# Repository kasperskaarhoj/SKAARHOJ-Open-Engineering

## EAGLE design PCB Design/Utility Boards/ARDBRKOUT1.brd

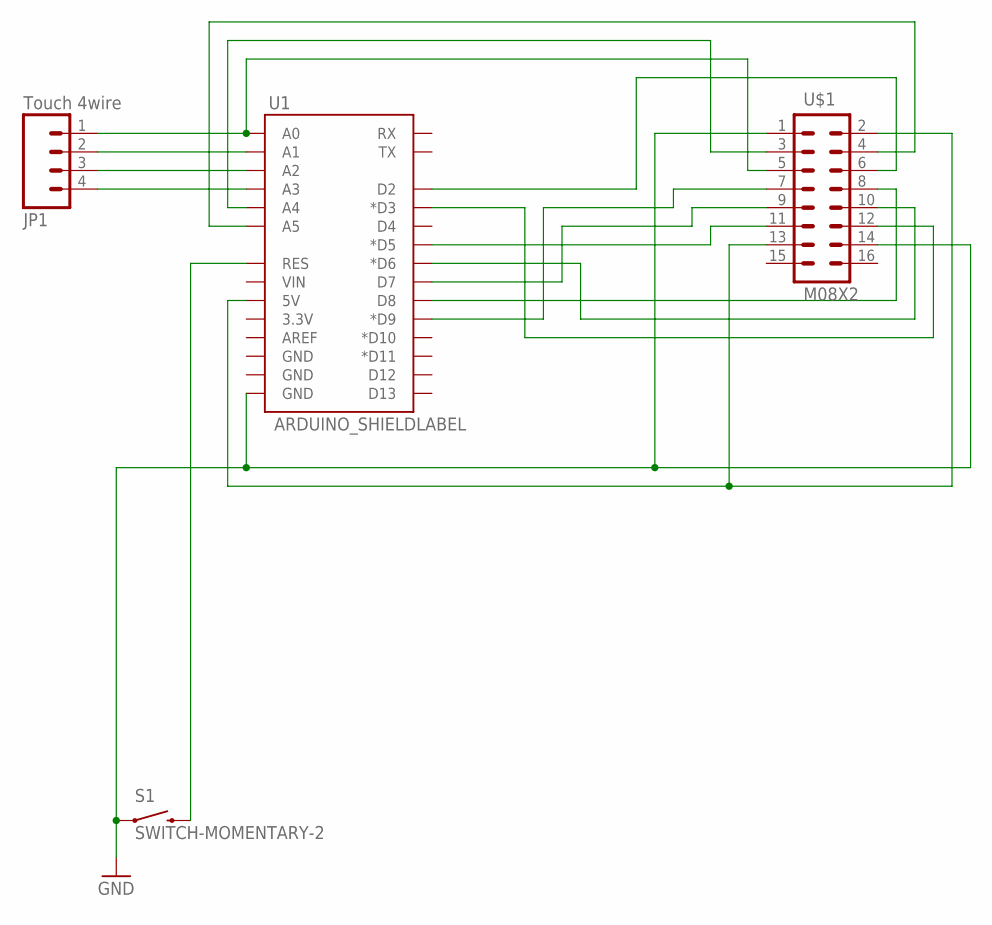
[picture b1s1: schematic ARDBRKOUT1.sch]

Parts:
JP1: Touch 4wire; 1X04
S1: SWITCH-MOMENTARY-2; TACTILE_SWITCH_TALL
U1: ARDUINO_SHIELDLABEL; DUEMILANOVE_SHIELD
U$1: M08X2; 2X8

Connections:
GND: S1.A2 (1), U1.GND@0 (GND), U$1.1, U$1.14
unnamed: U1.D9 (*D9), U$1.7
unnamed: U1.5V, U$1.2, U$1.13
unnamed: U1.A4, U$1.3
unnamed: U1.A5, U$1.4
unnamed: JP1.1, U1.A0, U$1.5
unnamed: U1.D2, U$1.6
unnamed: U1.D5 (*D5), U$1.11
unnamed: U1.D8, U$1.8
unnamed: U1.D7, U$1.9
unnamed: U1.D6 (*D6), U$1.10
unnamed: JP1.2, U1.A1
unnamed: U1.D3 (*D3), U$1.12
unnamed: JP1.3, U1.A2
unnamed: JP1.4, U1.A3
unnamed: S1.B2 (2), U1.RES

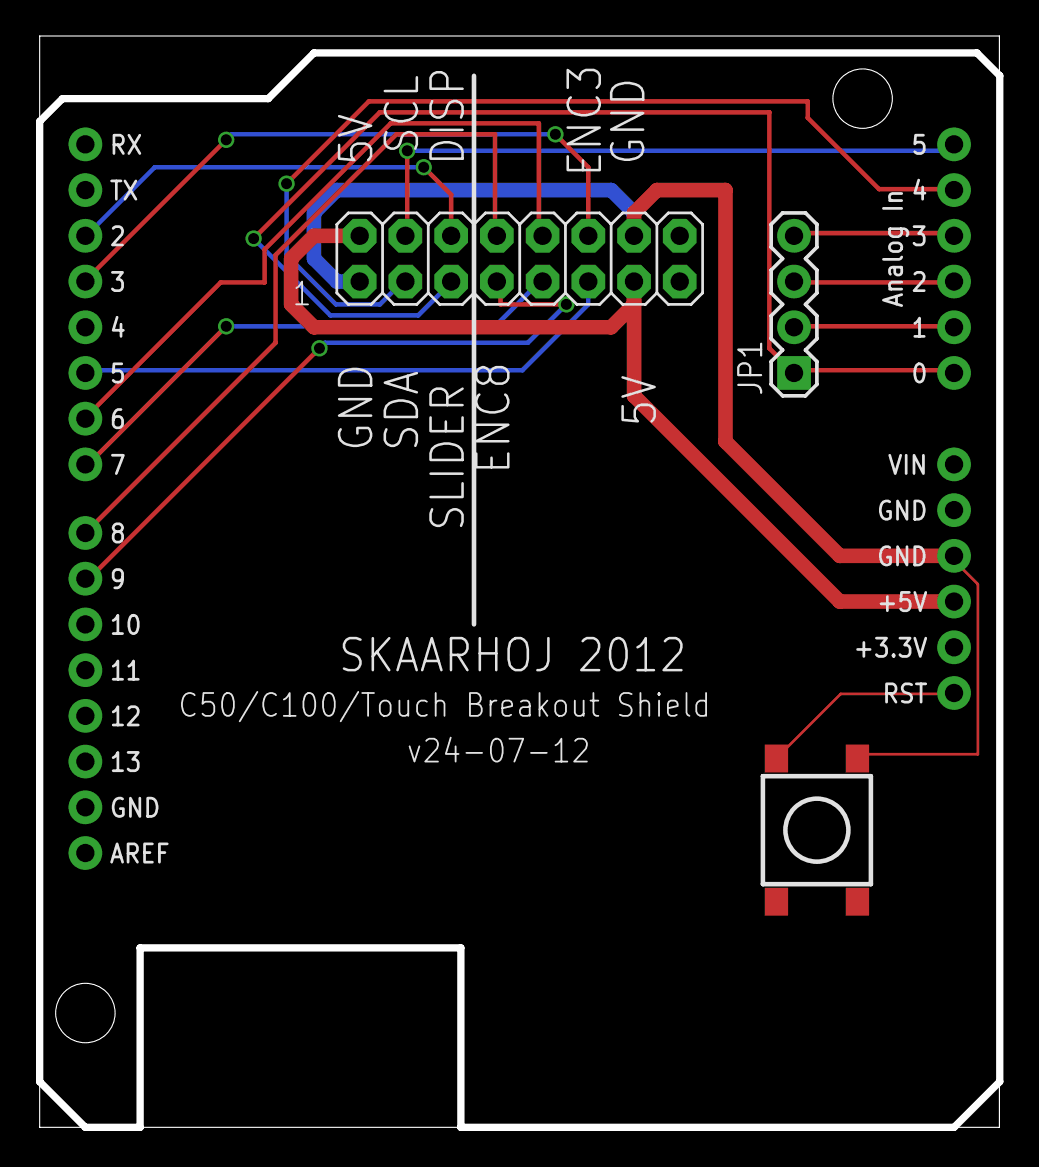
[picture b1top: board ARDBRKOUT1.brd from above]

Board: 2 copper layers, 53.3 x 60.6 mm, 4 parts (0 on the bottom side), 16 nets.

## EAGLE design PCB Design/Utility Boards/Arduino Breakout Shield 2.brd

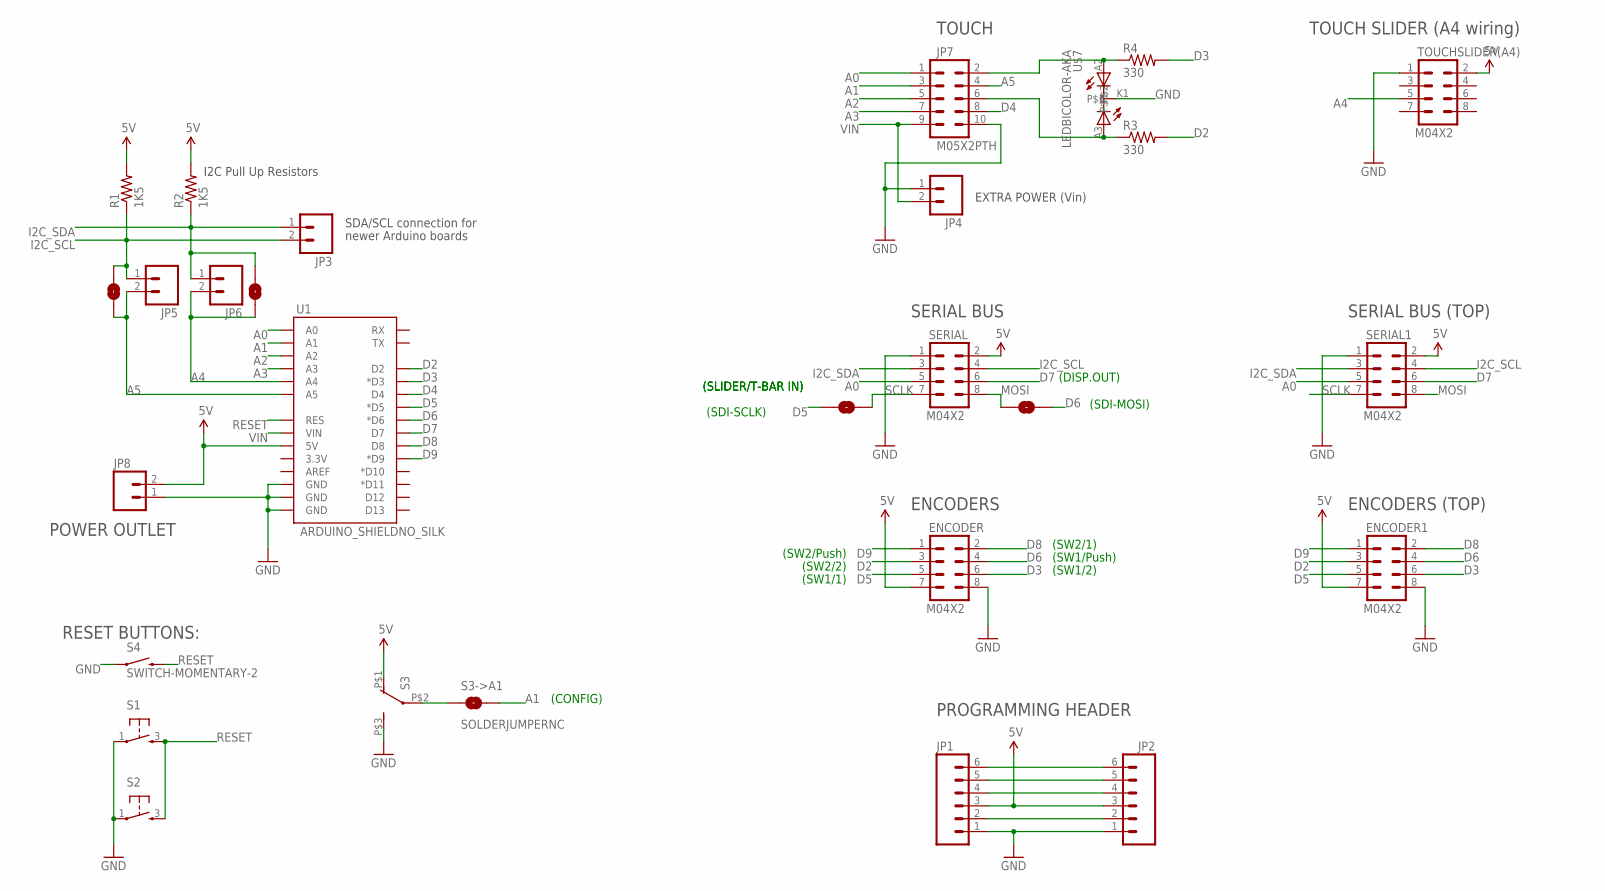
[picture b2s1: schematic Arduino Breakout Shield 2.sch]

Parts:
ENCODER, ENCODER1: M04X2; 2X4
JP1, JP2: M06POLAR; MOLEX-1X6
JP3, JP4, JP5, JP6: M02PTH; 1X02
JP7: M05X2PTH; AVR_ICSP
JP8: M02PTH4; 1X02_XTRA_BIG
MOSI->D6: SOLDERJUMPERNC; SJ_2S
R1, R2: 1K5; 0603-RES
R3, R4: 330; AXIAL-0.4
S1, S2: TAC_SWITCH; PUSHBUTTON
S3: SWITCH-DPST; TECONNECTIVITY-DPST
S3->A1, S3->A2, S3->A3: SOLDERJUMPERNC; SJ_2S
S4: SWITCH-MOMENTARY-2; TACTILE_SWITCH_TALL
SCLK->D5: SOLDERJUMPERNC; SJ_2S
SERIAL, SERIAL1: M04X2; 2X4
TOUCHSLIDER(A4): M04X2; 2X4
U1: ARDUINO_SHIELDNO_SILK; DUEMILANOVE_VIAS
U$7: LEDBICOLOR-AKA; LED5MM-BICOLOR

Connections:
5V: ENCODER.7, ENCODER1.7, JP1.3, JP2.3, JP8.2, R1.2, R2.2, S3.P$1 (O), SERIAL.2, SERIAL1.2, TOUCHSLIDER(A4).2, U1.5V
A0: JP7.1, SERIAL.5, SERIAL1.5, U1.A0
A1: JP7.3, S3->A1.2, U1.A1
A2: JP7.5, U1.A2
A3: JP7.7, U1.A3
A4: JP6.2, S3->A3.2, TOUCHSLIDER(A4).5, U1.A4
A5: JP5.2, JP7.4, S3->A2.2, U1.A5
D2: ENCODER.3, ENCODER1.3, R3.P$2 (2), U1.D2
D3: ENCODER.6, ENCODER1.6, R4.P$2 (2), U1.D3 (*D3)
D4: JP7.8, U1.D4
D5: ENCODER.5, ENCODER1.5, SCLK->D5.1, U1.D5 (*D5)
D6: ENCODER.4, ENCODER1.4, MOSI->D6.2, U1.D6 (*D6)
D7: SERIAL.6, SERIAL1.6, U1.D7
D8: ENCODER.2, ENCODER1.2, U1.D8
D9: ENCODER.1, ENCODER1.1, U1.D9 (*D9)
GND: ENCODER.8, ENCODER1.8, JP1.1, JP2.1, JP4.1, JP7.10, JP8.1, S1.1, S2.1, S3.P$3 (S), S4.A2 (1), SERIAL.1, SERIAL1.1, TOUCHSLIDER(A4).1, U1.GND@0 (GND), U1.GND@1 (GND), U1.GND@2 (GND), U$7.K1
I2C_SCL: JP3.2, JP5.1, R1.1, S3->A2.1, SERIAL.4, SERIAL1.4
I2C_SDA: JP3.1, JP6.1, R2.1, S3->A3.1, SERIAL.3, SERIAL1.3
MOSI: MOSI->D6.1, SERIAL.8, SERIAL1.8
unnamed: JP1.2, JP2.2
unnamed: S3.P$2, S3->A1.1
unnamed: JP7.2, R4.P$1 (1), U$7.A2
unnamed: JP7.6, R3.P$1 (1), U$7.A3
unnamed: JP1.4, JP2.4
unnamed: JP1.5, JP2.5
unnamed: JP1.6, JP2.6
RESET: S1.3, S2.3, S4.B2 (2), U1.RES
SCLK: SCLK->D5.2, SERIAL.7, SERIAL1.7
VIN: JP4.2, JP7.9, U1.VIN

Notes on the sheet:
PROGRAMMING HEADER
I2C Pull Up Resistors
SDA/SCL connection for
newer Arduino boards
ENCODERS
SERIAL BUS
TOUCH
POWER OUTLET
EXTRA POWER (Vin)
(SLIDER/T-BAR IN)
(SDI-SCLK)
(SDI-MOSI)
(SW2/Push)
(SW2/2)
(SW1/1)
(SW2/1)
(SW1/Push)
(SW1/2)
(CONFIG)
ENCODERS (TOP)
SERIAL BUS (TOP)
(DISP.OUT)
TOUCH SLIDER (A4 wiring)
RESET BUTTONS:

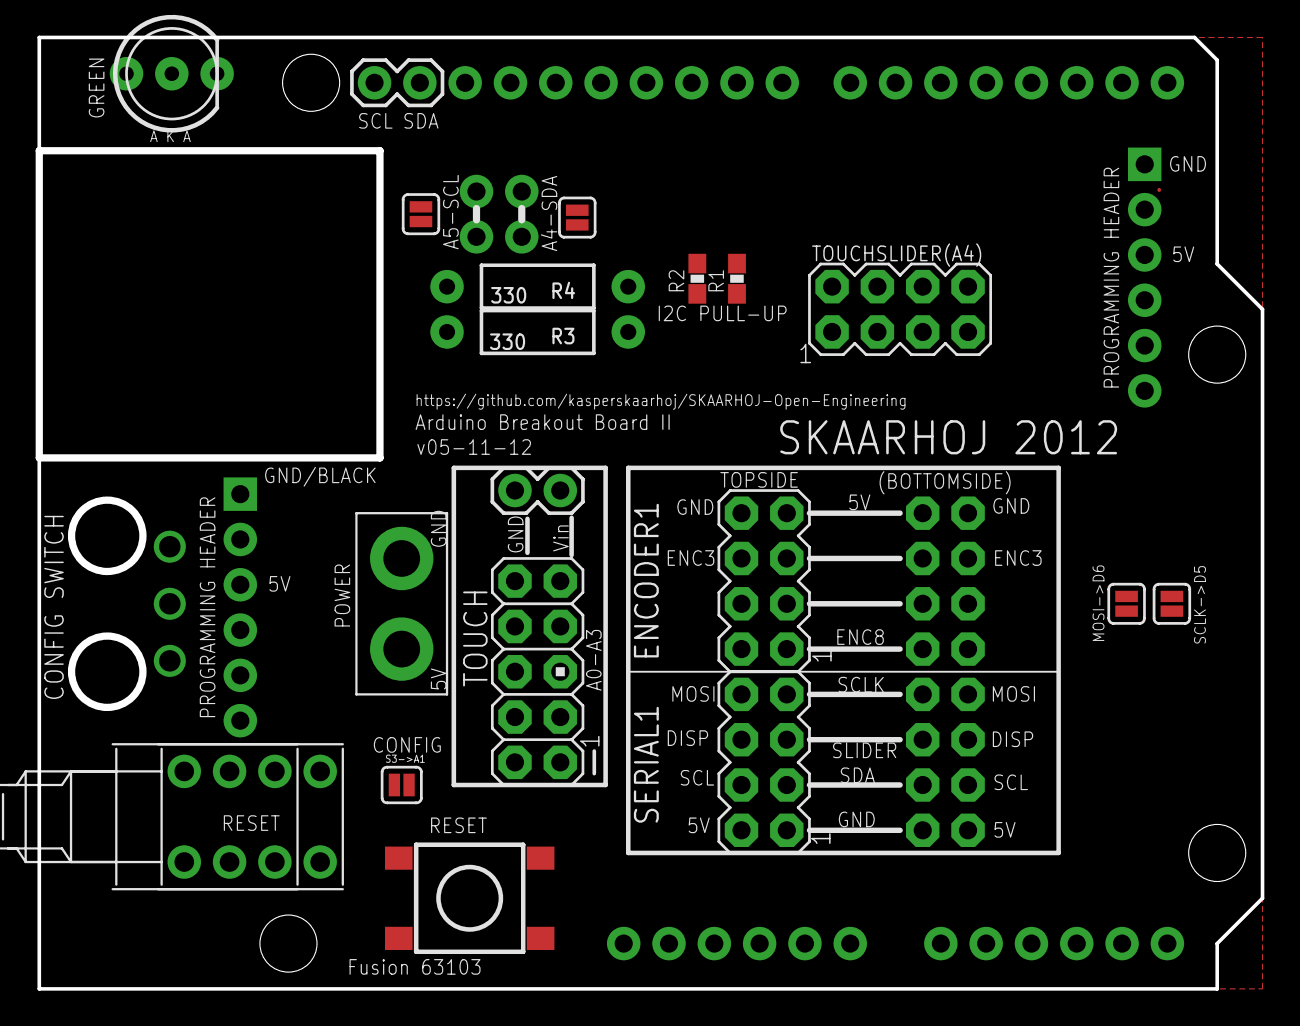
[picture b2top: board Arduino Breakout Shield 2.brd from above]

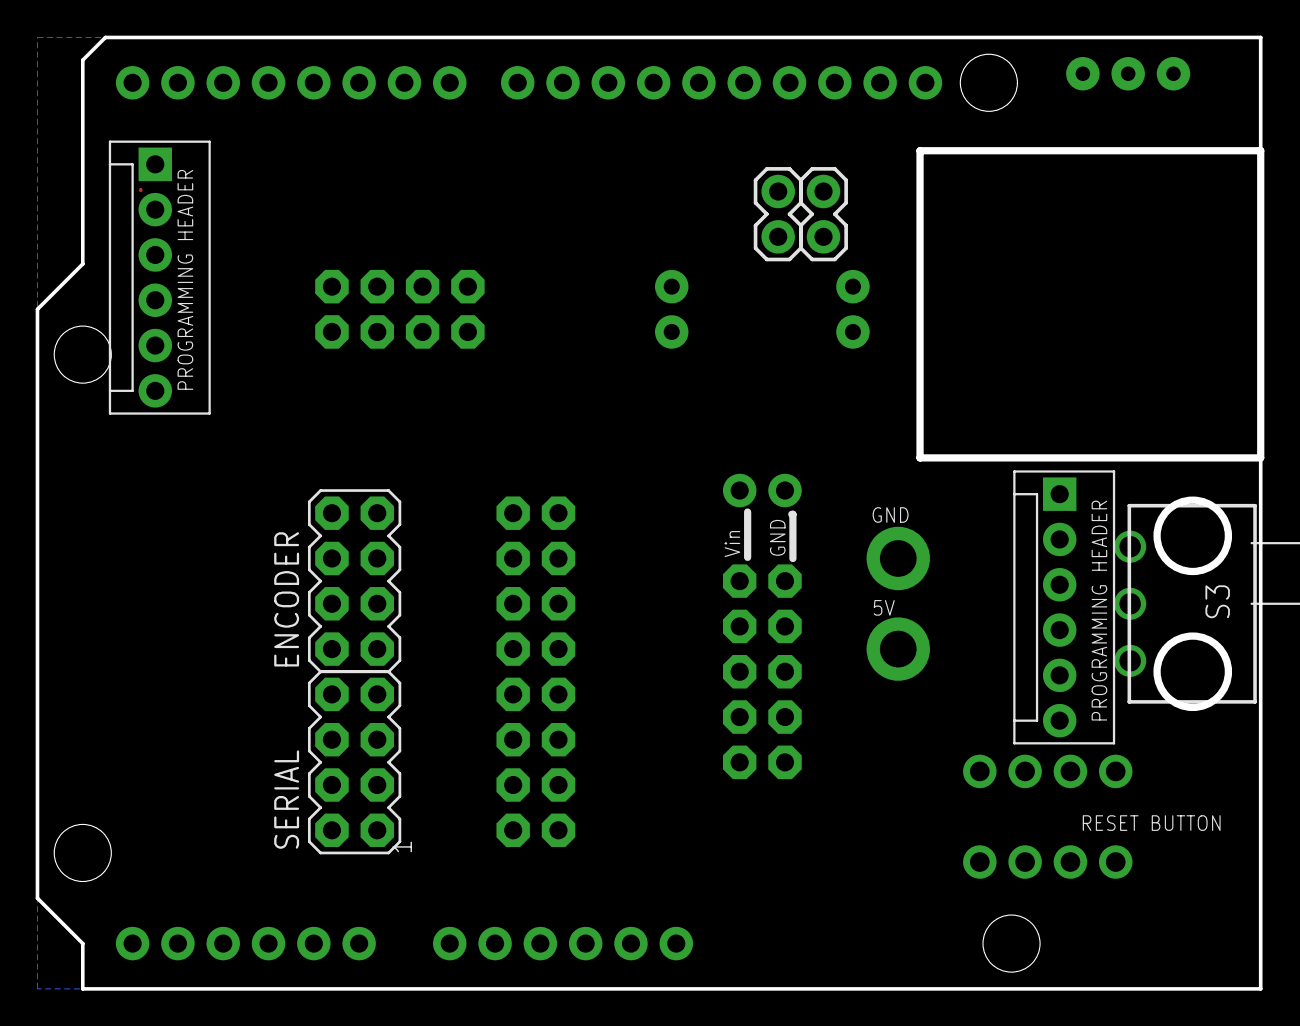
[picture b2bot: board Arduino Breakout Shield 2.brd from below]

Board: 2 copper layers, 68.6 x 53.3 mm, 29 parts (7 on the bottom side), 29 nets.

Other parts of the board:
U$8: ARDUINO-OUTLINE

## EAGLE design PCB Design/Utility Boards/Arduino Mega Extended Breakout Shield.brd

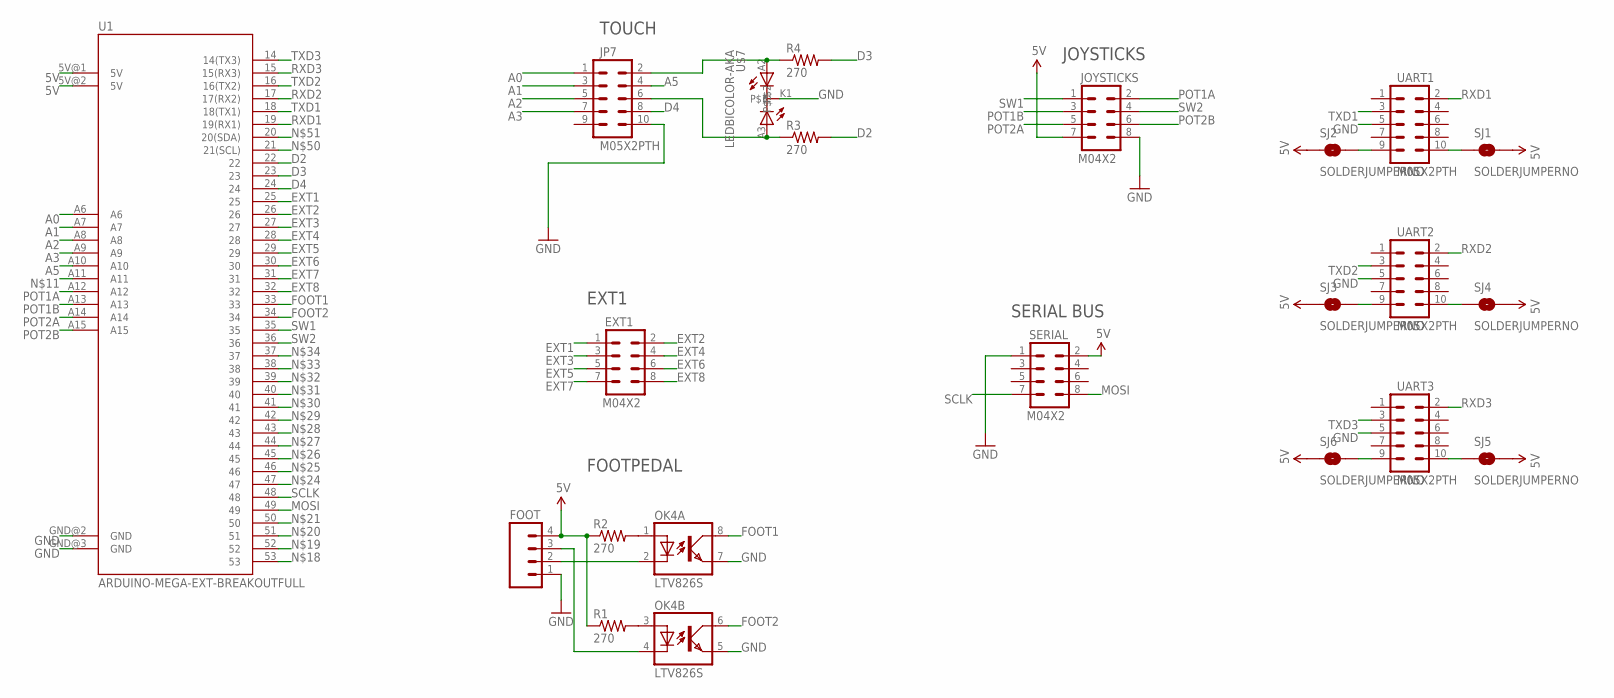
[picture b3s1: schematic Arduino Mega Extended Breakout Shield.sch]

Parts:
EXT1: M04X2; 2X4
FOOT: M04LOCK; 1X04_LOCK
JOYSTICKS: M04X2; 2X4
JP7: M05X2PTH; AVR_ICSP
OK4: LTV826S; DIL8-SMD
R1, R2, R3, R4: 270; 0603-RES
SERIAL: M04X2; 2X4
SJ1, SJ2, SJ3, SJ4, SJ5, SJ6: SOLDERJUMPERNO; SJ_2S-NO
U1: ARDUINO-MEGA-EXT-BREAKOUTFULL; ARDUINO_MEGA_EXT_BREAKOUT
U$7: LEDBICOLOR-AKA; LED5MM-BICOLOR
UART1, UART2, UART3: M05X2PTH; AVR_ICSP

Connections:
5V: FOOT.4, JOYSTICKS.7, R1.1, R2.1, SERIAL.2, SJ1.2, SJ2.1, SJ3.1, SJ4.2, SJ5.2, SJ6.1, U1.5V@1 (5V), U1.5V@2 (5V)
A0: JP7.1, U1.A6
A1: JP7.3, U1.A7
A2: JP7.5, U1.A8
A3: JP7.7, U1.A9
A5: JP7.4, U1.A10
D2: R3.2, U1.22
D3: R4.2, U1.23
D4: JP7.8, U1.24
EXT1: EXT1.1, U1.25
EXT2: EXT1.2, U1.26
EXT3: EXT1.3, U1.27
EXT4: EXT1.4, U1.28
EXT5: EXT1.5, U1.29
EXT6: EXT1.6, U1.30
EXT7: EXT1.7, U1.31
EXT8: EXT1.8, U1.32
FOOT1: OK4.8 (COL), U1.33
FOOT2: OK4.6 (COL), U1.34
GND: FOOT.1, JOYSTICKS.8, JP7.10, OK4.5 (EMIT), OK4.7 (EMIT), SERIAL.1, U1.GND@2 (GND), U1.GND@3 (GND), U$7.K1, UART1.5, UART2.5, UART3.5
MOSI: SERIAL.8, U1.49
unnamed: OK4.3 (A), R1.2
unnamed: OK4.1 (A), R2.2
unnamed: SJ6.2, UART3.9
unnamed: FOOT.2, OK4.2 (C)
unnamed: FOOT.3, OK4.4 (C)
unnamed: SJ3.2, UART2.9
unnamed: JP7.2, R4.1, U$7.A2
unnamed: JP7.6, R3.1, U$7.A3
unnamed: SJ2.2, UART1.9
unnamed: SJ1.1, UART1.10
unnamed: SJ4.1, UART2.10
unnamed: SJ5.1, UART3.10
POT1A: JOYSTICKS.2, U1.A12
POT1B: JOYSTICKS.3, U1.A13
POT2A: JOYSTICKS.5, U1.A14
POT2B: JOYSTICKS.6, U1.A15
RXD1: U1.19 (19(RX1)), UART1.2
RXD2: U1.17 (17(RX2)), UART2.2
RXD3: U1.15 (15(RX3)), UART3.2
SCLK: SERIAL.7, U1.48
SW1: JOYSTICKS.1, U1.35
SW2: JOYSTICKS.4, U1.36
TXD1: U1.18 (18(TX1)), UART1.3
TXD2: U1.16 (16(TX2)), UART2.3
TXD3: U1.14 (14(TX3)), UART3.3

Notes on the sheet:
TOUCH
SERIAL BUS
JOYSTICKS
EXT1
FOOTPEDAL

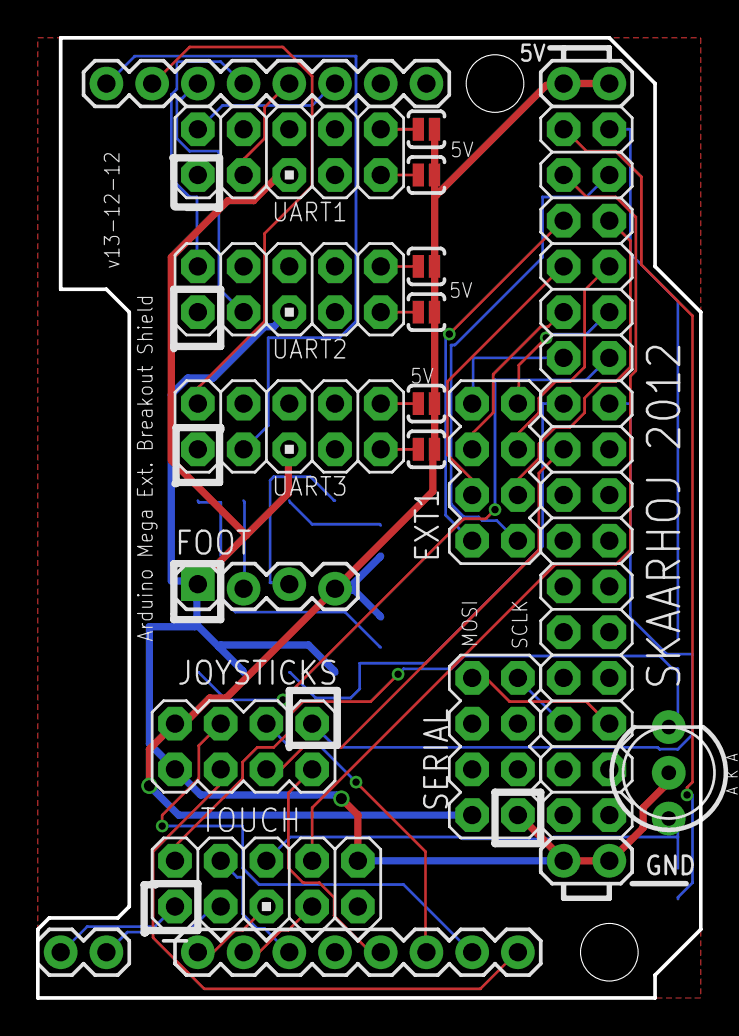
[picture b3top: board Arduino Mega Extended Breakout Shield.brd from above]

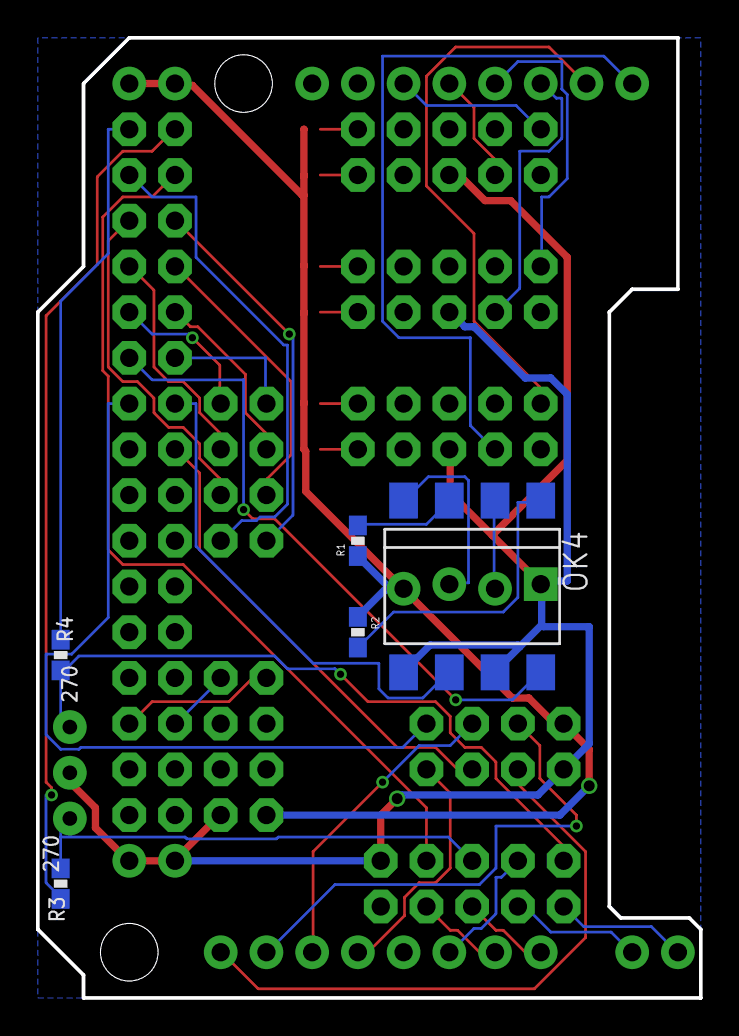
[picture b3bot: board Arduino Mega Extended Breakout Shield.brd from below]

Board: 2 copper layers, 36.8 x 53.3 mm, 21 parts (5 on the bottom side), 46 nets.

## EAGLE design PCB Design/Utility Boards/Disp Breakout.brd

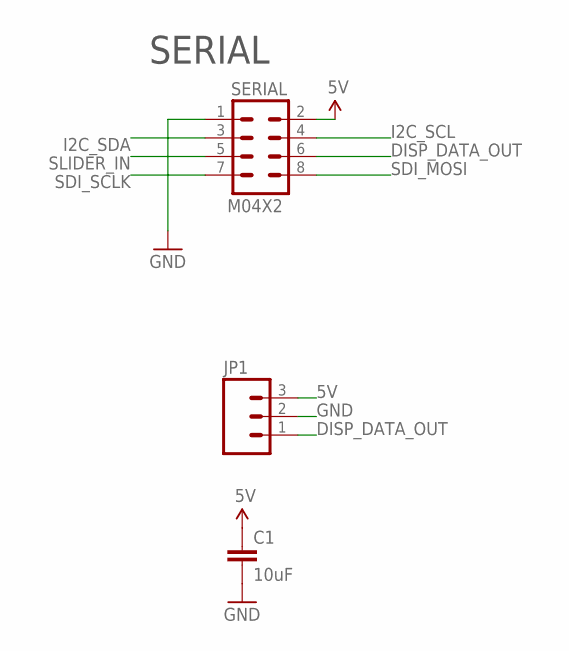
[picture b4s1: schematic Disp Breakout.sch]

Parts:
C1: 10uF; 0603-CAP
JP1: M03PTH; 1X03
SERIAL: M04X2; 2X4

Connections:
5V: C1.1, JP1.3, SERIAL.2
DISP_DATA_OUT: JP1.1, SERIAL.6
GND: C1.2, JP1.2, SERIAL.1
I2C_SCL: SERIAL.4
I2C_SDA: SERIAL.3
SDI_MOSI: SERIAL.8
SDI_SCLK: SERIAL.7
SLIDER_IN: SERIAL.5

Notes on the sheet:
SERIAL

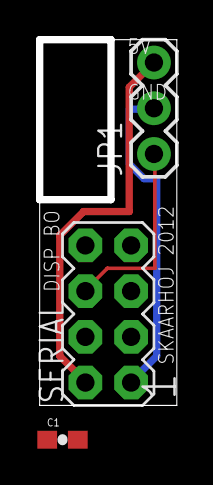
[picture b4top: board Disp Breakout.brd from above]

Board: 2 copper layers, 7.6 x 20.3 mm, 3 parts (0 on the bottom side), 3 nets.

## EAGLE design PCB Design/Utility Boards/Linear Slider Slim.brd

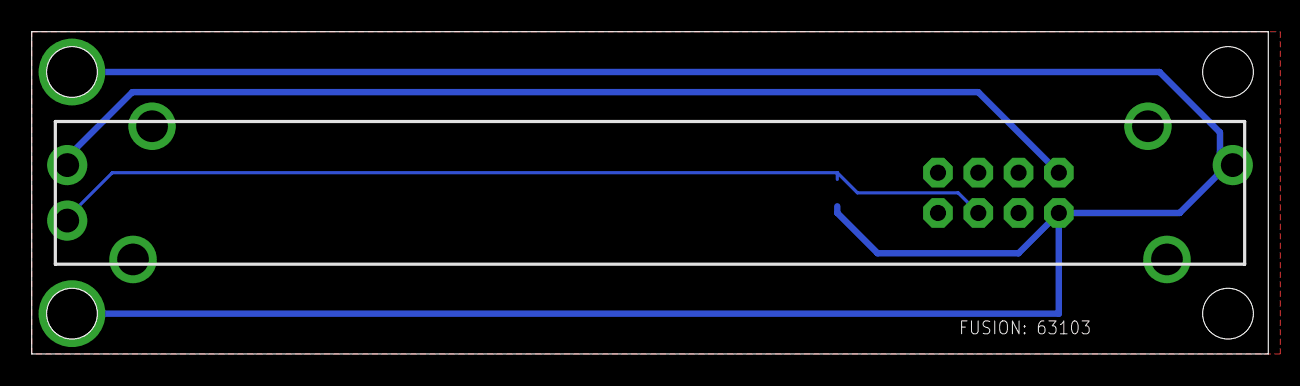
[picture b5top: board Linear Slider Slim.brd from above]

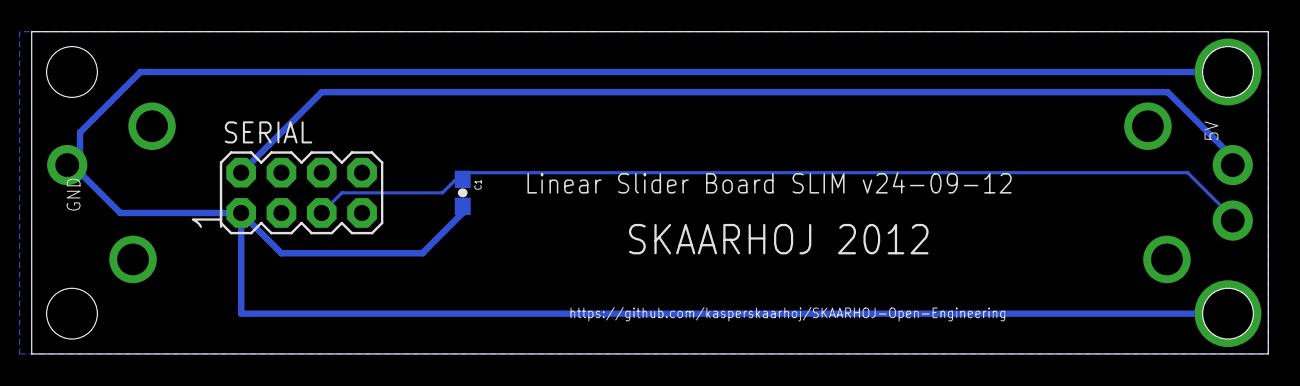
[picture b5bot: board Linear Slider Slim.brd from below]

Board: 2 copper layers, 78.0 x 20.3 mm, 3 parts (2 on the bottom side), 3 nets.

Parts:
C1: 10nF; 0603-CAP
POT1: 10K Linear; SLIDER60
SERIAL: M04X2; 2X4

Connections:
5V: POT1.1, SERIAL.2
GND: C1.2, POT1.3, SERIAL.1
SLIDER_IN: C1.1, POT1.2A, SERIAL.5

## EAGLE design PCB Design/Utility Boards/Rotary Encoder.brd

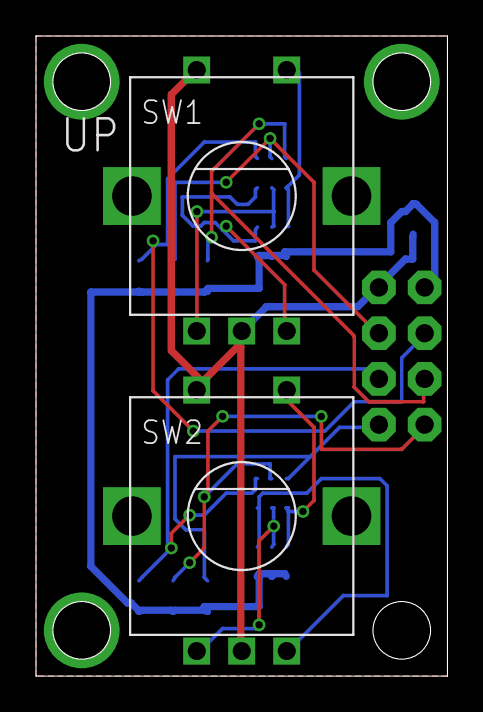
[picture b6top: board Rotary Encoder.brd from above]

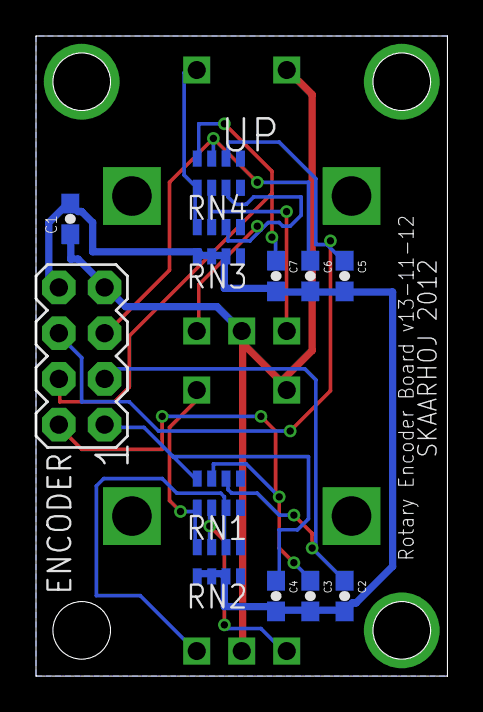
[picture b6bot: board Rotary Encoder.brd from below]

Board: 2 copper layers, 22.9 x 35.6 mm, 14 parts (12 on the bottom side), 14 nets.

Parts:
C1: 10uF; 0603-CAP
C2, C3, C4, C5, C6, C7: 100nF; 0603-CAP
ENCODER: M04X2; 2X4
RN1, RN4: 1K; CAY16_HAND
RN2, RN3: 10K; CAY16_HAND
SW1, SW2: EC12E_SW; ALPS_EC12E_SW

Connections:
5V: C1.1, ENCODER.7, SW1.C, SW1.D, SW2.C, SW2.D
D2: C2.1, ENCODER.3, RN1.6
D3: C5.1, ENCODER.6, RN4.6
D5: C6.1, ENCODER.5, RN4.7
D6: C7.1, ENCODER.4, RN4.8
D8: C3.1, ENCODER.2, RN1.7
D9: C4.1, ENCODER.1, RN1.8
GND: C1.2, C2.2, C3.2, C4.2, C5.2, C6.2, C7.2, ENCODER.8, RN2.1, RN2.2, RN2.3, RN3.1, RN3.2, RN3.3
unnamed: RN1.3, RN2.6, SW2.B
unnamed: RN3.6, RN4.3, SW1.B
unnamed: RN3.7, RN4.2, SW1.A
unnamed: RN1.2, RN2.7, SW2.A
unnamed: RN1.1, RN2.8, SW2.E
unnamed: RN3.8, RN4.1, SW1.E

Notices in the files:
parts and their libraries:
SparkFun: Licensing: CC v3.0 Share-Alike You are welcome to use this library for commercial purposes.
